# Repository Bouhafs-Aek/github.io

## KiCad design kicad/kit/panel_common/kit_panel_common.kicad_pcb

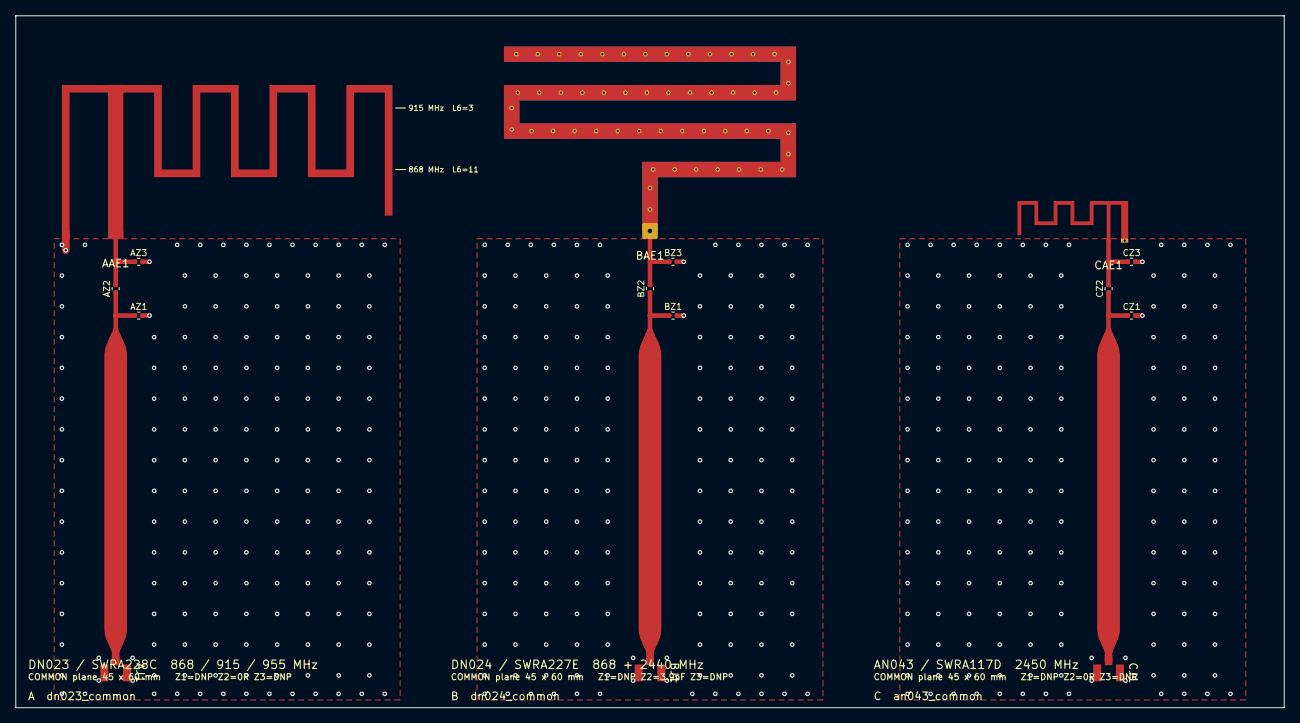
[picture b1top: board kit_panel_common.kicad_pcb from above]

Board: 2 copper layers, 165.0 x 90.0 mm, 15 parts (0 on the bottom side), 9 nets.

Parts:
AAE1: ANT_DN023_IFA; TI_DN023_IFA_868
AJ1: U.FL receptacle; U_FL_Hirose_U_FL_R_SMT_1_Vertical
AZ1, AZ3: DNP; Chip_0402_1005Metric_RF
AZ2: 0R; Chip_0402_1005Metric_RF
BAE1: ANT_DN024_Monopole; TI_DN024_Monopole_868_2440
BJ1: U.FL receptacle; U_FL_Hirose_U_FL_R_SMT_1_Vertical
BZ1, BZ3: DNP; Chip_0402_1005Metric_RF
BZ2: 3.9pF; Chip_0402_1005Metric_RF
CAE1: ANT_SWRA117D_2G4_Left; Texas_SWRA117D_2.4GHz_Left
CJ1: U.FL receptacle; U_FL_Hirose_U_FL_R_SMT_1_Vertical
CZ1, CZ3: DNP; Chip_0402_1005Metric_RF
CZ2: 0R; Chip_0402_1005Metric_RF

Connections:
ANT_FEED_A: AAE1.1 (FEED), AZ2.2 (ANT_FEED), AZ3.1 (ANT_FEED)
ANT_FEED_B: BAE1.1 (ANT_FEED), BZ2.2 (ANT_FEED), BZ3.1 (ANT_FEED)
ANT_FEED_C: CAE1.1 (ANT_FEED), CZ2.2 (ANT_FEED), CZ3.1 (ANT_FEED)
GND_A: AAE1.2 (SHORT), AJ1.2 (GND), AZ1.2 (GND), AZ3.2 (GND)
GND_B: BJ1.2 (GND), BZ1.2 (GND), BZ3.2 (GND)
GND_C: CAE1.2 (GND), CJ1.2 (GND), CZ1.2 (GND), CZ3.2 (GND)
RF_IN_A: AJ1.1 (SIGNAL), AZ1.1 (RF_IN), AZ2.1 (RF_IN)
RF_IN_B: BJ1.1 (SIGNAL), BZ1.1 (RF_IN), BZ2.1 (RF_IN)
RF_IN_C: CJ1.1 (SIGNAL), CZ1.1 (RF_IN), CZ2.1 (RF_IN)

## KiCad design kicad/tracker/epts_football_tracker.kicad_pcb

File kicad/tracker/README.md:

# Football GNSS tracker — an EPTS pod in KiCad

A wearable player tracker for football: a pod worn between the shoulder blades
in a vest, logging position, speed and inertial data for training analysis. In
the paper's terms it is an EPTS, an Electronic Performance and Tracking System.

It builds out the **future work** of

> L.A. Oliveira, R. García, D. Melendi, R. Oliveira, *A low-cost GNSS-based
> electronic performance and tracking system for sports: Design, validation,
> and accuracy enhancement through signal processing techniques*, Results in
> Engineering 32 (2026) 112596,
> [doi:10.1016/j.rineng.2026.112596](https://doi.org/10.1016/j.rineng.2026.112596).

Their prototype (a Maduino Zero A9G with a GPS-only receiver logging at 1 Hz)
reached 0.21 m mean error after outlier removal and an 11-sample moving
average. They list the limits themselves: 1 Hz misses sprints and changes of
direction, GPS-only suffers multipath, there is no IMU, and satellite count
and DOP were never logged. Their conclusion asks for "higher-frequency GNSS
modules" plus IMUs and sensor fusion. This board is that hardware:

| limitation in the paper | this board |
|---|---|
| GPS only, logged at 1 Hz | **u-blox NEO-M9N**: GPS, Galileo, GLONASS and BeiDou, up to 25 Hz. It is the module the paper names as preferable. |
| no IMU ("does not eliminate the need for sensor fusion (IMU)") | **ST ISM330DHCX**: ±16 g, ±4000 dps, up to 6.67 kHz, on its own SPI bus |
| satellites and HDOP not stored | UBX over UART: `NAV-PVT` carries numSV, pDOP and hAcc/sAcc in every epoch |
| devices aligned afterwards by timestamp matching | **TIMEPULSE (PPS)** wired to the MCU, so every pod samples on GNSS time |
| microSD, raw CSV ("open data") | microSD kept, in SPI mode, for raw UBX + IMU logs |
| GPRS for live data, needs a SIM | **nRF52840** (Raytac MDBT50Q-1MV2): BLE for live status, USB for download |
| 3.7 V 1800 mAh Li-Po, > 20 h | same cell, with a **USB-C charger** and load sharing on board |
| 54 × 80 × 16 mm enclosure | 42 × 72 mm board, so it fits that same enclosure |

## What is in the project

```
kicad/
├── tracker/
│   ├── epts_football_tracker.kicad_pro   net classes: GNSS_50R, Power, USB
│   ├── epts_football_tracker.kicad_sch   A3, one sheet, 46 parts
│   ├── epts_football_tracker.kicad_pcb   4 layer, 42 x 72 mm, placed + RF routed
│   └── sym-lib-table / fp-lib-table      -> ../library/EPTS_Tracker.*
├── library/
│   ├── EPTS_Tracker.kicad_sym            19 symbols, from KiCad 9.0.9.1
│   └── EPTS_Tracker.pretty/              18 footprints from KiCad 9.0.9.1 + the patch
└── tools/
    ├── gen_tracker_library.py            fetches and flattens the library parts
    ├── gen_tracker_project.py            writes schematic, board and project
    ├── tracker_router.py                 GND fan-out and power-net maze router
    └── check_tracker.py                  netlist, ERC, electrical and RF checks
```

**State of the board: placed, power and RF routed, signals left to route.**

Already laid down and checked:

* the GNSS patch and its ground, the 50 Ω feed, the matching pads, the via
  fences and the BLE antenna keep-out
* **a GND via beside every top-layer ground pad**, each joined to its pad by
  a short track, so every ground pin reaches the In1/In2 planes directly
* **all four power nets** (VBUS, VBAT, VSYS, +3V3), every pad, at 0.4 mm
  where they fit and 0.2–0.25 mm into fine-pitch pads. The long trunks run
  on B.Cu to leave the top for signals.

What is left is 34 signal nets, about 45 connections: GNSS UART and PPS, the
IMU and microSD SPI buses, USB D+/D-, SWD, button, LEDs and the battery
divider. Route them in KiCad, then press **B** to fill the four GND pours.

## Block diagram

```
 25 mm patch ── CPWG 50 Ω ── Z3/Z2/Z1 ── NEO-M9N ──UART + PPS + EXTINT + RESET──┐
                                                                              │
 ISM330DHCX ──────────── SPI (own bus) + INT1/INT2 ─────────────────── MDBT50Q (nRF52840)
                                                                              │  BLE, chip antenna
 microSD (SPI) ────────────────────── SPI + card detect ──────────────────────┤
                                                                              │
 USB-C ─ USBLC6 ─ D+/D- ──────────────────────────────────────────────────────┘
   │
   └─ VBUS ─ MCP73831 (500 mA) ─ VBAT ─ 1S Li-Po 1800 mAh
        └── D1 ─┐       Q1 ──────┘
                VSYS ─ AP2112K-3.3 ─ +3V3 → everything
```

## Parts

| ref | part | why this one |
|---|---|---|
| U1 | u-blox **NEO-M9N** | 4 constellations, 25 Hz. It shares the NEO footprint with the NEO-6M the paper used, so the result is directly comparable. |
| AE1 | 25 × 25 × 4 mm passive ceramic L1 patch | Sits on the top GND pour, sky side. The NEO-M9N has its own SAW and LNA, so no active antenna supply is needed. |
| Z1–Z3 | 0402 pi network | Z2 is fitted as a 0 Ω link; Z1 and Z3 are not fitted. It is there to retune the patch inside the case, the same convention as the antenna boards in this repo. |
| U2 | Raytac **MDBT50Q-1MV2** (nRF52840) | BLE 5 plus native USB in a pre-certified module with its own antenna |
| U3 | ST **ISM330DHCX** | Industrial 6-axis IMU. At ±16 g it covers running and jumping; a slide tackle or a ball strike to the back can exceed it. |
| J3 | Hirose **DM3AT** microSD | The paper's open-data store, push-push with card detect |
| U4 | Microchip **MCP73831-2** | 4.20 V single-cell charger; R7 = 2.0 kΩ sets 500 mA (0.28 C) |
| Q1, D1 | AO3401A + B5819WS | Load sharing: the system runs from USB while the cell charges |
| U5 | Diodes **AP2112K-3.3** | 600 mA LDO, 55 µA quiescent |
| J1, U6 | GCT USB4105 USB-C + USBLC6-2SC6 | Sink-only (5.1 kΩ Rd on CC1/CC2), ESD on D+/D-/VBUS |
| J2 | JST-PH 2-pin SMD | Battery. Pin 1 is +. **Check your cell's cable**: Li-Po vendors do not agree on JST polarity. |
| J4 | Tag-Connect TC2030-NL | SWD with no header fitted (VCC, SWDIO, SWCLK, nRESET, SWO) |
| SW1, D2, D3 | button, status LED, charge LED | The button starts and stops a session and wakes the MCU from System OFF |

All symbols and footprints except the patch are copies of the official KiCad
library parts, pinned to tag `9.0.9.1`. Their pin tables are the ones the
checker reads. The one generated footprint is the patch, and it has one
part-specific dimension: **the feed pin's offset from the centre**
(`PATCH_FEED_OFFSET`, 1.5 mm). Set it from the drawing of the patch you buy
and regenerate the library and the board.

## Firmware pin map

Printed by `check_tracker.py` from the schematic itself, so it cannot go stale:

| nRF52840 | net | | nRF52840 | net |
|---|---|---|---|---|
| P0.08 | GNSS_TXD (UARTE RX) | | P0.20 | IMU_SCK |
| P0.06 | GNSS_RXD (UARTE TX) | | P0.21 | IMU_MOSI |
| P0.13 | GNSS_PPS | | P0.22 | IMU_MISO |
| P0.14 | GNSS_EXTINT | | P0.23 | IMU_CS |
| P0.15 | GNSS_RESET_N | | P0.24 / P0.25 | IMU_INT1 / IMU_INT2 |
| P0.26 | SD_SCK | | P0.02 (AIN0) | VBAT_SENSE = VBAT / 2 |
| P0.27 | SD_MOSI | | P1.06 | BTN (internal pull-up) |
| P0.07 | SD_MISO | | P1.07 | LED_K (active low) |
| P0.11 | SD_CS | | P0.18 | nRESET (SWD) |
| P0.12 | SD_DET (internal pull-up) | | P1.00 | SWO |

Before committing to this map, check it against the nRF52840 product
specification's table of GPIOs near the radio. Nordic recommends low-drive,
low-frequency use for some of those pins. The SD and IMU clocks were kept on
P0 pins for that reason, but the checker cannot read that table.

## The GNSS front end

* **The patch sits on the board's top GND pour**, which is part of the
  antenna. Nothing else is placed within 1 mm of it, and the checker enforces
  that. Vias under the ceramic are tented.
* **The feed runs on the bottom layer**, because the top copper under the
  patch is ground. From the feed pin it is a grounded coplanar waveguide on
  B.Cu over the In2 GND plane, then a via up to the top layer at the pi
  network, then into RF_IN (pad 11).
* **50 Ω on this stackup is w = 0.38 mm with a 0.30 mm gap.** The stackup is
  JLC04161H-7628, with a 0.2104 mm prepreg at εr 4.4 between each outer layer
  and its plane. `line_impedance.cpwg` gives 51.4 Ω, and the checker requires
  45–55 Ω. The gap is the netclass clearance of `GNSS_50R`, so the pour keeps
  it automatically.
* **Via fences** run along both sides of the feed. The total feed length is
  25 mm.
* **The BLE module's antenna overhangs nothing.** It sits on the right board
  edge, and a keep-out on all four copper layers runs from the module's own
  keep-out to the board edge.

## Power budget (estimate; check each figure against the data sheets)

| consumer | typical | note |
|---|---|---|
| NEO-M9N, continuous tracking | ~35 mA | depends on constellations and rate |
| nRF52840: logging, BLE advertising | ~3 mA | mostly asleep between samples |
| ISM330DHCX, high-performance mode | ~1 mA | |
| microSD, averaged over buffered writes | ~5 mA | card dependent |
| LDO quiescent, divider, leakage | < 0.1 mA | |
| **total** | **~45 mA** | 1800 mAh → **~35–40 h** |

A match is 90 minutes and a training session 2 hours, so this leaves days
between charges. The figure that dominates is the GNSS module's, so the
power-save modes in the u-blox integration manual are the place to start if
you need more.

## Running it

```sh
python3 kicad/tools/gen_tracker_library.py   # only to refresh the library (needs network)
python3 kicad/tools/gen_tracker_project.py   # schematic, board, project (~70 s, needs numpy)
python3 kicad/tools/check_tracker.py         # must end with "all checks passed"
```

`check_tracker.py` reads only the files KiCad reads and never imports the
generator. It is this project's stand-in for ERC, because CI has no KiCad
install, and it checks:

* **netlist**: every schematic pin's net is derived from the wires, labels and
  no-connect flags in the `.kicad_sch`, and must equal the net on the matching
  board pad
* **ERC**: no floating pins, no single-pin nets, every power input driven
  (PWR_FLAG on GND, VBUS and VSYS), at most one output per net
* **electrical**:
  * every supply pin within its absolute maximum
  * the full cell at the ADC at 2.10 V
  * charge current 500 mA = 0.28 C
  * USB-C Rd resistors present
  * u-blox requirements: VDD_USB to GND with USB unused, D_SEL open for
    UART, RF_IN reaching the patch only through the pi network
  * ISM330DHCX unused aux pins handled
  * SD pull-ups present
  * SWD on P0.18 / P1.00
* **board**:
  * a closed Edge.Cuts outline
  * every pad-to-pad gap at or above its net classes' clearance, and every
    pad at least `min_hole_clearance` from any hole. This is the pad-level
    part of KiCad's DRC.
  * one RF width at 50 Ω on both outer layers
  * an unbroken copper path from the patch feed through Z2 to RF_IN
  * no GND via inside the feed gap
  * no courtyard overlaps
  * nothing near the patch, nothing in the BLE keep-out
  * every via clear of other nets' pads
  * every track and via clear of other nets' copper, holes, the board edge
    and the keep-outs, by exact segment and rectangle distances
  * each power net joined into one piece by KiCad's own rule: a track end
    or via joins only the copper it lies inside
  * every top-layer GND pad has its own via

The checker was mutation-tested. Renaming one net label and widening one feed
segment each make it fail with the right message, and the generated files
pass. The checker caught one real bug during development: the pi network's
route assumed the C_0402 pad offset (0.48 mm) for an R_0402 (0.51 mm).

### Clearance rules, and why they are 0.15 mm

The netclass clearance and `min_hole_clearance` are both 0.15 mm, not KiCad's
0.2 mm default, because two library land patterns need it:

* the ISM330DHCX's LGA-14 lands are 0.150–0.175 mm apart
* the USB4105's outer GND pads are 0.194 mm from its locating holes

Both are within a 4-layer fab's minimums (about 0.09–0.1 mm). The first KiCad
DRC run on this design flagged exactly these pads, and the checker now
reproduces them.

**Open `epts_football_tracker.kicad_pcb`. Do not start a new board** with
*Update PCB from Schematic*. A new board has no outline, every footprint
piled in reference order, and the RF feed unrouted. Its DRC then reports
`invalid_outline`, dozens of silkscreen overlaps and the feed as
unconnected, none of which apply to the generated layout.

## Open items before ordering boards

1. **Route the remaining signals** in KiCad, fill zones, then run ERC and DRC.
2. **Patch feed offset**: set `PATCH_FEED_OFFSET` from the chosen part.
3. **Battery polarity** at J2: match the cell's cable.
4. **Enclosure and patch tuning**: a plastic case and the wearer's back detune
   the patch. Measure inside the case, and use Z1–Z3 if it has moved, the same
   procedure as the antenna boards in this repo.
5. **Firmware** is not part of this project. The hardware assumes UBX
   `NAV-PVT` at 10–25 Hz over UART, IMU FIFO reads on INT1, and logs written
   to microSD, with PPS-aligned timestamps so the paper's post-processing
   (outlier removal, then an 11-sample moving average, or IMU fusion) can run
   on the raw data.

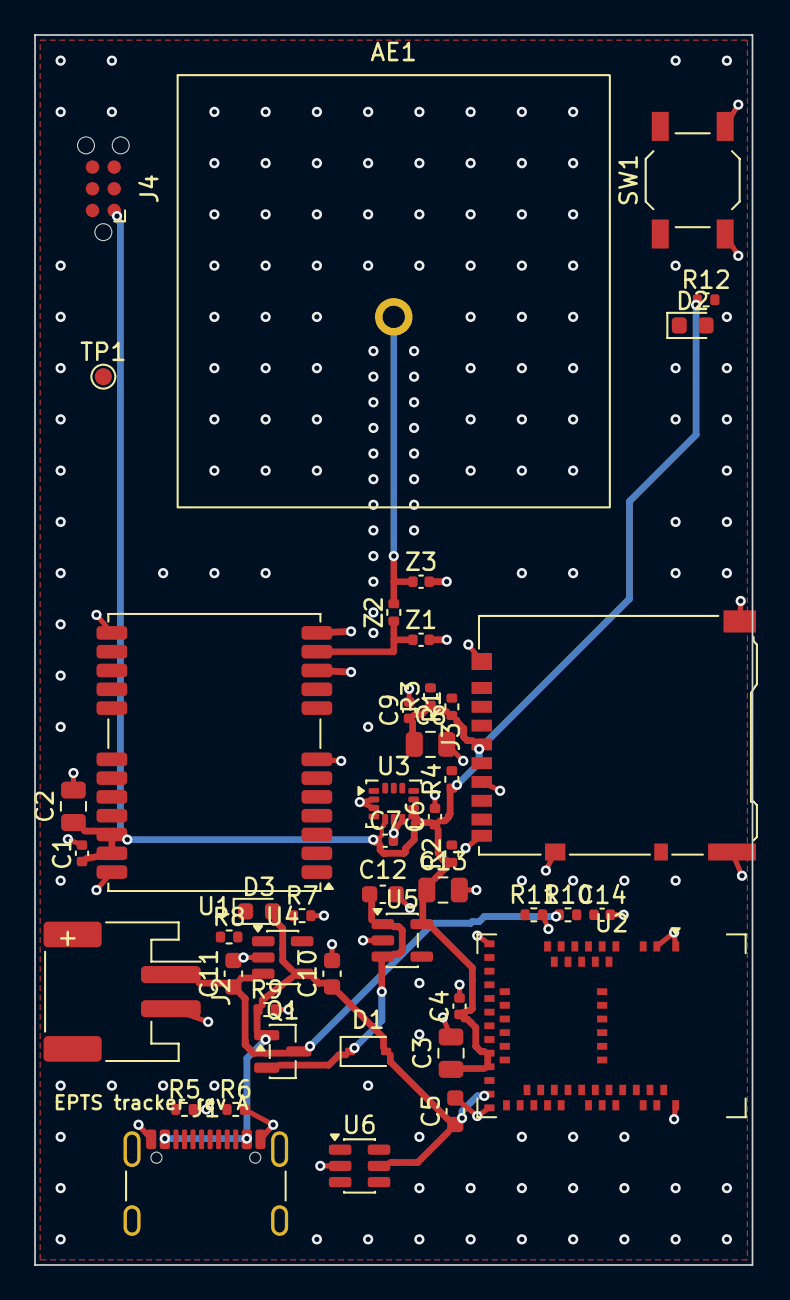
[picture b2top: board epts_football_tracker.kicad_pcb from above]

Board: 4 copper layers, 42.0 x 72.0 mm, 46 parts (0 on the bottom side), 41 nets.

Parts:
AE1: GNSS patch 25x25; GNSS_Patch_25x25mm_SingleFeed
C1, C4, C6, C7, C9, C14: 100nF; C_0402_1005Metric
C2, C3, C8, C13: 10uF; C_0805_2012Metric
C5, C10, C11, C12: 4.7uF; C_0603_1608Metric
D1: B5819WS; D_SOD-323
D2: green; LED_0603_1608Metric
D3: orange; LED_0603_1608Metric
J1: USB4105-GF-A; USB_C_Receptacle_GCT_USB4105-xx-A_16P_TopMnt_Horizontal
J2: Li-Po 1S; JST_PH_S2B-PH-SM4-TB_1x02-1MP_P2.00mm_Horizontal
J3: DM3AT-SF-PEJM5; microSD_HC_Hirose_DM3AT-SF-PEJM5
J4: TC2030-IDC-NL; Tag-Connect_TC2030-IDC-NL_2x03_P1.27mm_Vertical
Q1: AO3401A; SOT-23
R1, R2, R3, R4: 47k; R_0402_1005Metric
R5, R6: 5.1k; R_0402_1005Metric
R7: 2.0k; R_0402_1005Metric
R8: 1k; R_0402_1005Metric
R9: 100k; R_0402_1005Metric
R10, R11: 1M; R_0402_1005Metric
R12: 470R; R_0402_1005Metric
SW1: TL3342; SW_SPST_TL3342
TP1: SAFEBOOT_N; TestPoint_Pad_D1.0mm
U1: NEO-M9N-00B; ublox_NEO
U2: MDBT50Q-1MV2; Raytac_MDBT50Q
U3: ISM330DHCX; LGA-14_3x2.5mm_P0.5mm_LayoutBorder3x4y
U4: MCP73831-2-OT; SOT-23-5
U5: AP2112K-3.3; SOT-23-5
U6: USBLC6-2SC6; SOT-23-6
Z1, Z3: DNP; C_0402_1005Metric
Z2: 0R; R_0402_1005Metric

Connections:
+3V3: C1.1 (+3V3), C2.1 (+3V3), C3.1 (+3V3), C4.1 (+3V3), C6.1 (+3V3), C7.1 (+3V3), C8.1 (+3V3), C9.1 (+3V3), C13.1 (+3V3), J3.4 (+3V3), J4.1 (+3V3), R1.1 (+3V3), R2.1 (+3V3), R3.1 (+3V3), R4.1 (+3V3), R12.1 (+3V3), U1.22 (+3V3), U1.23 (+3V3), U2.28 (+3V3), U2.30 (+3V3), U3.5 (+3V3), U3.8 (+3V3), U5.5 (+3V3)
BTN: SW1.1 (BTN), U2.57 (BTN)
CC1: J1.A5 (CC1), R5.1 (CC1)
CC2: J1.B5 (CC2), R6.1 (CC2)
CHG_LED: D3.1 (CHG_LED), R8.1 (CHG_LED)
CHG_PROG: R7.1 (CHG_PROG), U4.5 (CHG_PROG)
CHG_STAT: R8.2 (CHG_STAT), U4.1 (CHG_STAT)
GND: C1.2 (GND), C2.2 (GND), C3.2 (GND), C4.2 (GND), C5.2 (GND), C6.2 (GND), C7.2 (GND), C8.2 (GND), C9.2 (GND), C10.2 (GND), C11.2 (GND), C12.2 (GND), C13.2 (GND), C14.2 (GND), J1.A1 (GND), J1.A12 (GND), J1.B1 (GND), J1.B12 (GND), J1.S1 (GND), J2.2 (GND), J3.6 (GND), J3.9 (GND), J3.11 (GND), J4.5 (GND), R5.2 (GND), R6.2 (GND), R7.2 (GND), R9.2 (GND), R11.2 (GND), SW1.2 (GND), U1.7 (GND), U1.10 (GND), U1.12 (GND), U1.13 (GND), U1.24 (GND), U2.1 (GND), U2.2 (GND), U2.15 (GND), U2.33 (GND), U2.55 (GND), U3.2 (GND), U3.3 (GND), U3.6 (GND), U3.7 (GND), U4.2 (GND), U5.2 (GND), U6.2 (GND), Z1.2 (GND), Z3.2 (GND)
GNSS_ANT: AE1.1 (GNSS_ANT), Z2.2 (GNSS_ANT), Z3.1 (GNSS_ANT)
GNSS_EXTINT: U1.4 (GNSS_EXTINT), U2.36 (GNSS_EXTINT)
GNSS_PPS: U1.3 (GNSS_PPS), U2.37 (GNSS_PPS)
GNSS_RESET_N: U1.8 (GNSS_RESET_N), U2.39 (GNSS_RESET_N)
GNSS_RF: U1.11 (GNSS_RF), Z1.1 (GNSS_RF), Z2.1 (GNSS_RF)
GNSS_RXD: U1.21 (GNSS_RXD), U2.22 (GNSS_RXD)
GNSS_SAFEBOOT_N: TP1.1 (GNSS_SAFEBOOT_N), U1.1 (GNSS_SAFEBOOT_N)
GNSS_TXD: U1.20 (GNSS_TXD), U2.24 (GNSS_TXD)
IMU_CS: U2.45 (IMU_CS), U3.12 (IMU_CS)
IMU_INT1: U2.48 (IMU_INT1), U3.4 (IMU_INT1)
IMU_INT2: U2.49 (IMU_INT2), U3.9 (IMU_INT2)
IMU_MISO: U2.46 (IMU_MISO), U3.1 (IMU_MISO)
IMU_MOSI: U2.43 (IMU_MOSI), U3.14 (IMU_MOSI)
IMU_SCK: U2.44 (IMU_SCK), U3.13 (IMU_SCK)
LED_A: D2.2 (LED_A), R12.2 (LED_A)
LED_K: D2.1 (LED_K), U2.58 (LED_K)
NRESET: J4.3 (NRESET), U2.40 (NRESET)
SD_CS: J3.2 (SD_CS), R1.2 (SD_CS), U2.27 (SD_CS)
SD_DAT1: J3.8 (SD_DAT1), R2.2 (SD_DAT1)
SD_DAT2: J3.1 (SD_DAT2), R3.2 (SD_DAT2)
SD_DET: J3.10 (SD_DET), U2.29 (SD_DET)
SD_MISO: J3.7 (SD_MISO), R4.2 (SD_MISO), U2.23 (SD_MISO)
SD_MOSI: J3.3 (SD_MOSI), U2.16 (SD_MOSI)
SD_SCK: J3.5 (SD_SCK), U2.19 (SD_SCK)
SWDCLK: J4.4 (SWDCLK), U2.53 (SWDCLK)
SWDIO: J4.2 (SWDIO), U2.51 (SWDIO)
SWO: J4.6 (SWO), U2.47 (SWO)
USB_DN: J1.A7 (USB_DN), J1.B7 (USB_DN), U2.34 (USB_DN), U6.3 (USB_DN), U6.4 (USB_DN)
USB_DP: J1.A6 (USB_DP), J1.B6 (USB_DP), U2.35 (USB_DP), U6.1 (USB_DP), U6.6 (USB_DP)
VBAT: C11.1 (VBAT), J2.1 (VBAT), Q1.3 (VBAT), R10.1 (VBAT), U4.3 (VBAT)
VBAT_SENSE: C14.1 (VBAT_SENSE), R10.2 (VBAT_SENSE), R11.1 (VBAT_SENSE), U2.11 (VBAT_SENSE)
VBUS: C5.1 (VBUS), C10.1 (VBUS), D1.2 (VBUS), D3.2 (VBUS), J1.A4 (VBUS), J1.A9 (VBUS), J1.B4 (VBUS), J1.B9 (VBUS), Q1.1 (VBUS), R9.1 (VBUS), U2.32 (VBUS), U4.4 (VBUS), U6.5 (VBUS)
VSYS: C12.1 (VSYS), D1.1 (VSYS), Q1.2 (VSYS), U5.1 (VSYS), U5.3 (VSYS)
